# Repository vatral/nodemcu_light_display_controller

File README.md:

# NodeMCU light display controller

Controls a set of signs

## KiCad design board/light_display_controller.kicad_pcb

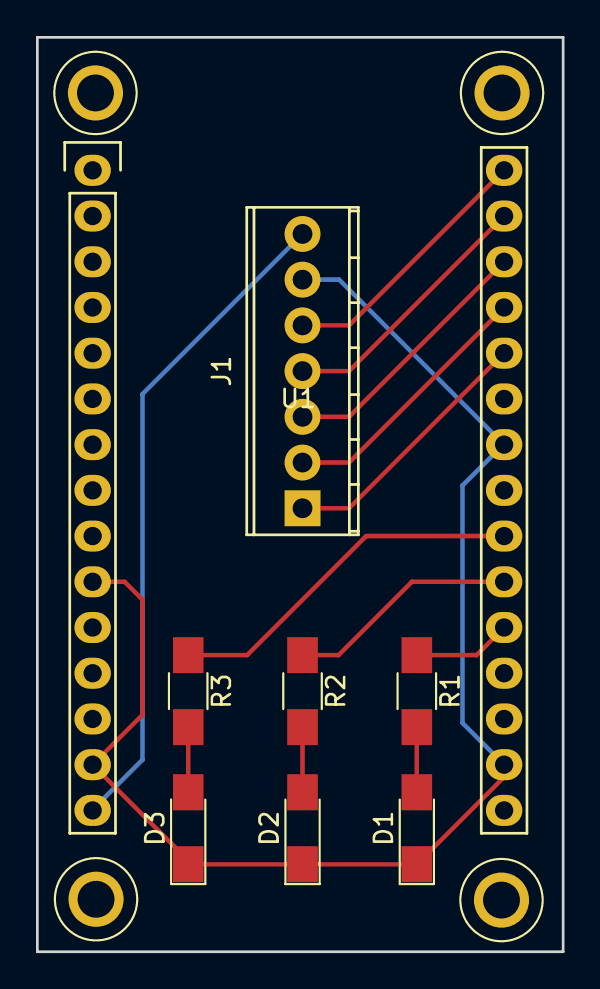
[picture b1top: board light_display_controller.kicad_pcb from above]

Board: 2 copper layers, 29.2 x 50.8 mm, 8 parts (0 on the bottom side), 13 nets.

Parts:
D1, D2, D3: LED; LED_1206_HandSoldering
J1: Screw_Terminal_1x07; TerminalBlock_Phoenix_MPT-2.54mm_7pol
R1, R2, R3: R; R_1206_HandSoldering
U1: NodeMCU_Amica_R2

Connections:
GND: D1.1, D2.1, D3.1, J1.6, U1.10, U1.14, U1.17, U1.24
unnamed: D1.2, R1.2
unnamed: D2.2, R2.2
unnamed: D3.2, R3.2
unnamed: J1.1, U1.26
unnamed: J1.2, U1.27
unnamed: J1.3, U1.28
unnamed: J1.4, U1.29
unnamed: J1.5, U1.30
unnamed: R1.1, U1.20
unnamed: R2.1, U1.21
unnamed: R3.1, U1.22
Vin: J1.7, U1.15

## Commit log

2018-09-18 Initial version
